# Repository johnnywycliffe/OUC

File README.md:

# Open Underglow Controller (OUC)
This project is designed to provide a better underglow control scheme than the one that comes with the LED strips. It has it's own controls, a small OLED screen, and a connector to the CANBUS for connecting to the car.

## Features
 - ESP 32 controller for fast LED updates
 - 256-bit colors for millions of colors
 - Configuarable patterns for uniqueness
 - Animations!
 - Brakes and turn signal controls for extended light modes
 - 4 12v channels to drive Underglow
 - 2 5v channels to drive extra underglow strips
 - CAN BUS connection to use LEDs as car gauges
 - Wifi/Bluetooth mode for phone control
 - Optional screen and joystick controls to bypass need for phone

## Hardware 
In this project are PCB files needed to order a board, parts files for having a board assembled, and 3d files for a 3d printing a case.

A full hardware list can be found in docs/hardware.md

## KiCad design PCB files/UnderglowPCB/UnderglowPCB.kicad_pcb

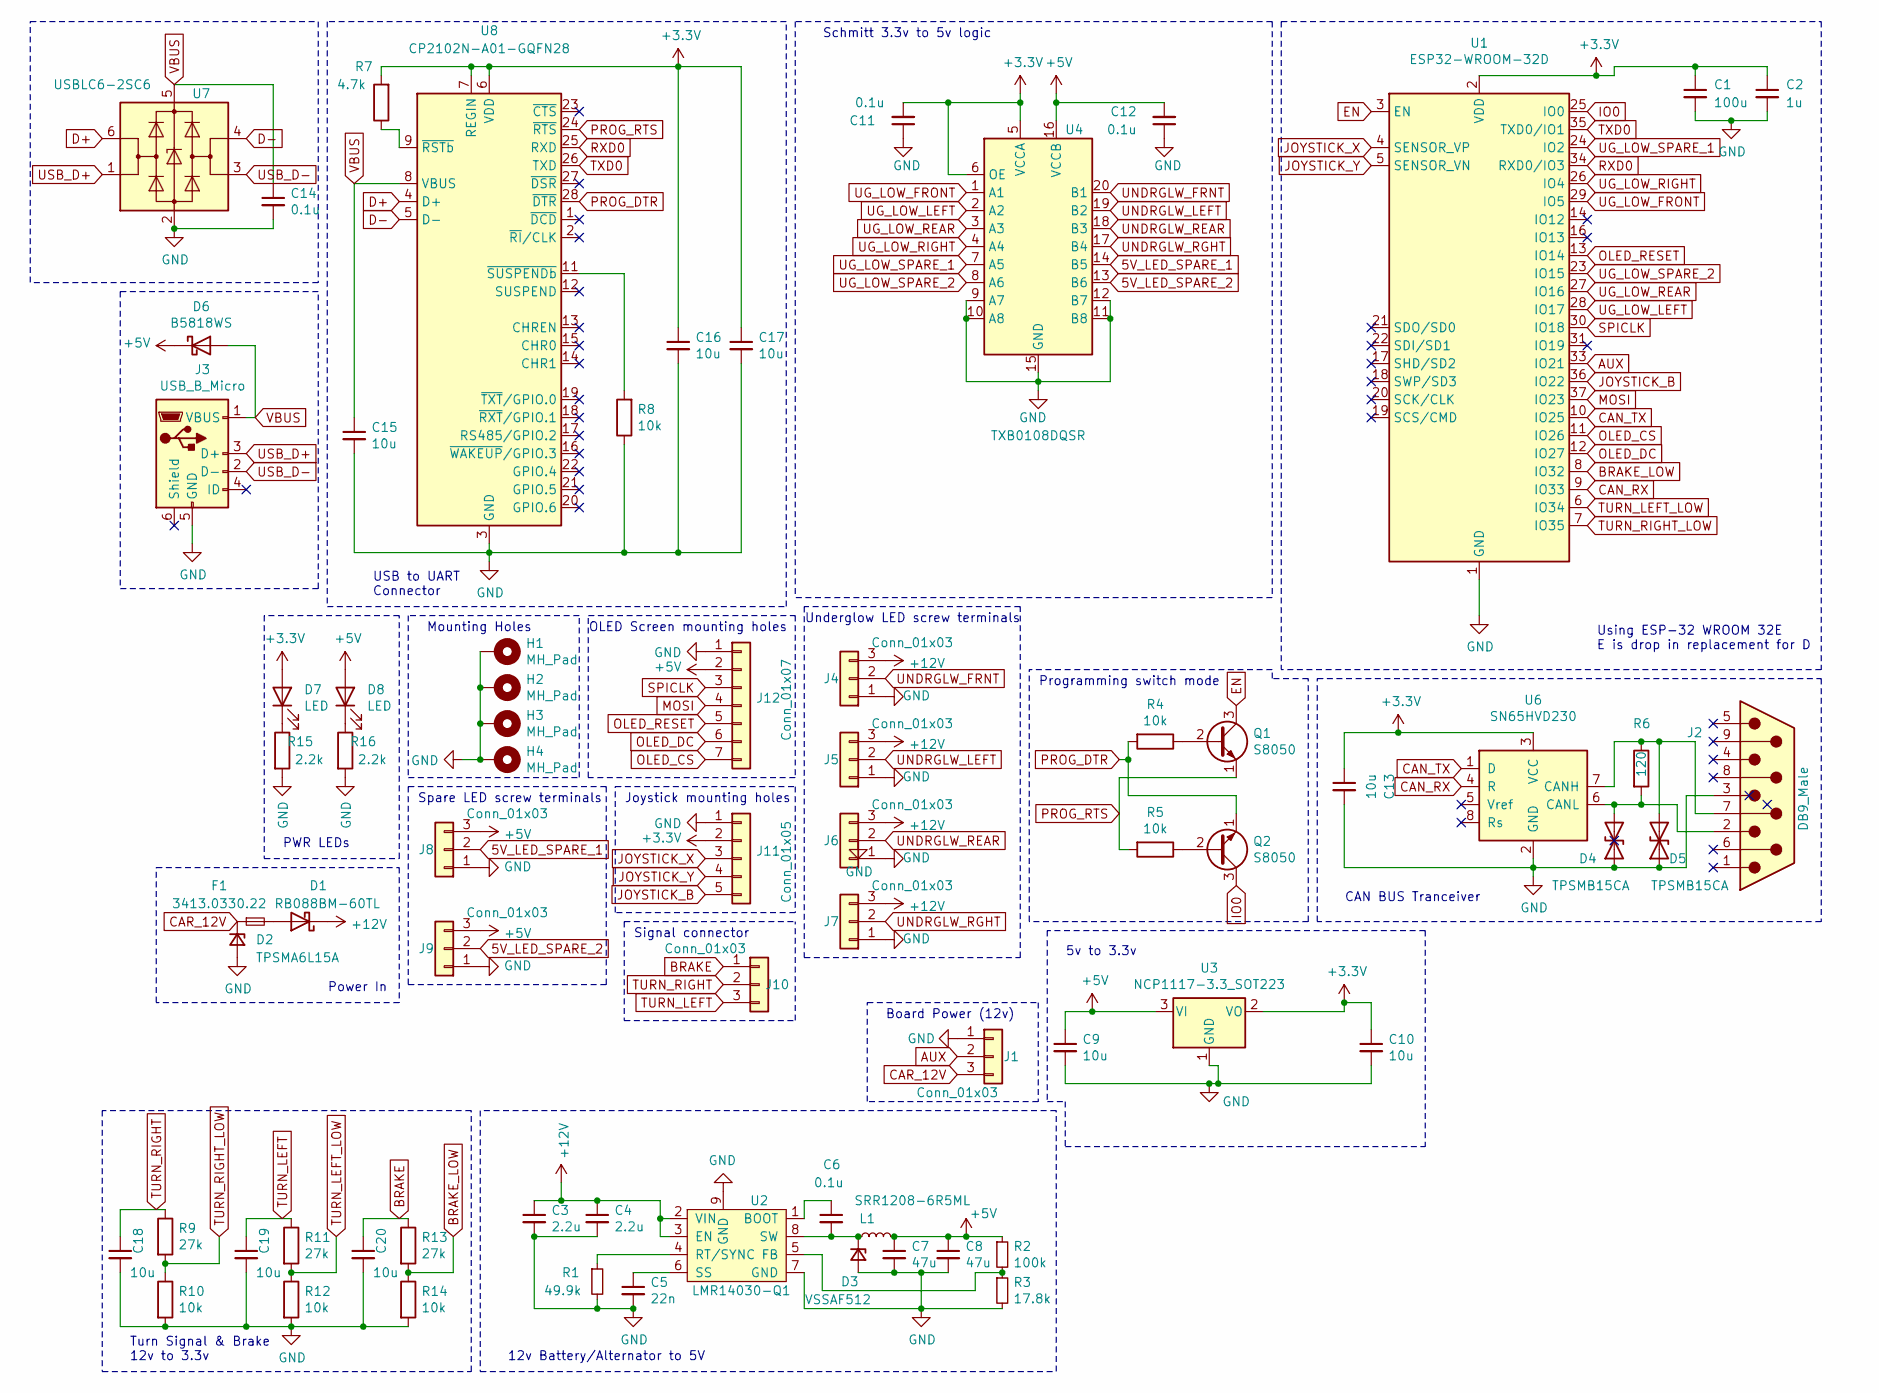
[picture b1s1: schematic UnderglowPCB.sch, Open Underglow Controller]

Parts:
C1: 100u; C_1210_3225Metric
C2: 1u; C_0402_1005Metric
C3, C4: 2.2u; C_0603_1608Metric
C5: 22n; C_0603_1608Metric
C6, C11, C12, C14: 0.1u; C_0603_1608Metric
C7, C8: 47u; C_1210_3225Metric
C9, C10, C13, C15, C16, C17, C18, C19, C20: 10u; C_0603_1608Metric
D1: RB088BM-60TL; TO-252-2_TabPin1
D2: TPSMA6L15A
D3: VSSAF512; DO-221AC
D4, D5: TPSMB15CA
D6: B5818WS; D_SOD-323
D7, D8: LED; LED_0603_1608Metric
F1: 3413.0330.22; Fuse_1206_3216Metric
H1, H2, H3, H4: MH_Pad; MountingHole_4.3mm_M4_Pad_Via
J1, J4, J5, J6, J7, J8, J9, J10: Conn_01x03; PinHeader_1x03_P2.54mm_Vertical
J2: DB9_Male; DB9
J3: USB_B_Micro; USB_Micro-AB_Molex_47590-0001
J11: Conn_01x05; Joystick_Header
J12: Conn_01x07; SSD1306_Footprint
L1: SRR1208-6R5ML; SRR1208
Q1, Q2: S8050; SOT-23
R1: 49.9k; R_0603_1608Metric
R2: 100k; R_0603_1608Metric
R3: 17.8k; R_0603_1608Metric
R4, R5, R8, R10, R12, R14: 10k; R_0603_1608Metric
R6: 120; R_0603_1608Metric
R7: 4.7k; R_0603_1608Metric
R9, R11, R13: 27k; R_0603_1608Metric
R15, R16: 2.2k; R_0603_1608Metric
U1: ESP32-WROOM-32D; ESP32-WROOM-32
U2: LMR14030-Q1; Texas_HSOP-8-1EP_3.9x4.9mm_P1.27mm_ThermalVias
U3: NCP1117-3.3_SOT223; SOT-223-3_TabPin2
U4: TXB0108DQSR; USON-20_2x4mm_P0.4mm
U6: SN65HVD230; Texas_HSOP-8-1EP_3.9x4.9mm_P1.27mm_ThermalVias
U7: USBLC6-2SC6; SOT-23-6
U8: CP2102N-A01-GQFN28; QFN-28-1EP_5x5mm_P0.5mm_EP3.35x3.35mm

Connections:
5V_LED_SPARE_1: J8.2, U4.14 (B5)
5V_LED_SPARE_2: J9.2, U4.13 (B6)
+3V3: C1.1, C2.1, C10.1, C11.2, C13.1, C16.1, C17.1, D7.2 (A), J11.2, R7.2, U1.2 (VDD), U3.2 (VO), U4.5 (VCCA), U4.6 (OE), U6.3 (VCC), U8.6 (VDD), U8.7 (REGIN)
+5V: C7.1, C8.1, C9.1, C12.2, D6.1 (K), D8.2 (A), J8.3, J9.3, J12.2, L1.2, R2.1, U3.3 (VI), U4.16 (VCCB)
+12V: C3.1, C4.1, D1.1 (K), J4.3, J5.3, J6.3, J7.3, U2.2 (VIN), U2.3 (EN)
AUX: J1.2, U1.33 (IO21)
BRAKE: C20.1, J10.1, R13.1
BRAKE_LOW: R13.2, R14.1, U1.8 (IO32)
CAN_RX: U1.9 (IO33), U6.4 (R)
CAN_TX: U1.10 (IO25), U6.1 (D)
CAR_12V: D2.1 (K), F1.1, J1.3
D+: U7.6 (I/O1), U8.4 (D+)
D-: U7.4 (I/O2), U8.5 (D-)
EN: Q1.3 (C), U1.3 (EN)
GND: C1.2, C2.2, C3.2, C4.2, C5.2, C7.2, C8.2, C9.2, C10.2, C11.1, C12.1, C13.2, C14.2, C15.2, C16.2, C17.2, C18.2, C19.2, C20.2, D2.2 (A), D3.2 (A), D4.1 (A1), D5.1 (A1), H1.1, H2.1, H3.1, H4.1, J1.1, J2.3, J3.5 (GND), J4.1, J5.1, J6.1, J7.1, J8.1, J9.1, J11.1, J12.1, R1.2, R3.2, R8.1, R10.2, R12.2, R14.2, R15.2, R16.2, U1.1 (GND), U1.15 (GND), U1.38 (GND), U1.39 (GND), U2.7 (GND), U2.9 (GND), U3.1 (GND), U4.9 (A7), U4.10 (A8), U4.11 (B8), U4.12 (B7), U4.15 (GND), U6.2 (GND), U7.2 (GND), U8.3 (GND), U8.29 (GND)
IO0: Q2.3 (C), U1.25 (IO0)
JOYSTICK_B: J11.5, U1.36 (IO22)
JOYSTICK_X: J11.3, U1.4 (SENSOR_VP)
JOYSTICK_Y: J11.4, U1.5 (SENSOR_VN)
MOSI: J12.4, U1.37 (IO23)
unnamed: C5.1, U2.6 (SS)
unnamed: C6.1, U2.1 (BOOT)
unnamed: C6.2, D3.1 (K), L1.1, U2.8 (SW)
unnamed: D1.2 (A), F1.2
unnamed: D4.2 (A2), J2.2, R6.2, U6.6 (CANL)
unnamed: D5.2 (A2), J2.7, R6.1, U6.7 (CANH)
unnamed: D7.1 (K), R15.1
unnamed: D8.1 (K), R16.1
unnamed: Q1.2 (B), R4.1
unnamed: Q2.2 (B), R5.1
unnamed: R1.1, U2.4 (RT/SYNC)
unnamed: R2.2, R3.1, U2.5 (FB)
unnamed: R7.1, U8.9 (~RSTb)
unnamed: R8.2, U8.11 (~SUSPENDb)
OLED_CS: J12.7, U1.11 (IO26)
OLED_DC: J12.6, U1.12 (IO27)
OLED_RESET: J12.5, U1.13 (IO14)
PROG_DTR: Q2.1 (E), R4.2, U8.28 (~DTR)
PROG_RTS: Q1.1 (E), R5.2, U8.24 (~RTS)
RXD0: U1.34 (RXD0/IO3), U8.25 (RXD)
SPICLK: J12.3, U1.30 (IO18)
TURN_LEFT: C19.1, J10.3, R11.1
TURN_LEFT_LOW: R11.2, R12.1, U1.6 (IO34)
TURN_RIGHT: C18.1, J10.2, R9.1
TURN_RIGHT_LOW: R9.2, R10.1, U1.7 (IO35)
TXD0: U1.35 (TXD0/IO1), U8.26 (TXD)
UG_LOW_FRONT: U1.29 (IO5), U4.1 (A1)
UG_LOW_LEFT: U1.28 (IO17), U4.2 (A2)
UG_LOW_REAR: U1.27 (IO16), U4.3 (A3)
UG_LOW_RIGHT: U1.26 (IO4), U4.4 (A4)
UG_LOW_SPARE_1: U1.24 (IO2), U4.7 (A5)
UG_LOW_SPARE_2: U1.23 (IO15), U4.8 (A6)
UNDRGLW_FRNT: J4.2, U4.20 (B1)
UNDRGLW_LEFT: J5.2, U4.19 (B2)
UNDRGLW_REAR: J6.2, U4.18 (B3)
UNDRGLW_RGHT: J7.2, U4.17 (B4)
USB_D+: J3.3 (D+), U7.1 (I/O1)
USB_D-: J3.2 (D-), U7.3 (I/O2)
VBUS: C14.1, C15.1, D6.2 (A), J3.1 (VBUS), U7.5 (VBUS), U8.8 (VBUS)

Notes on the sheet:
12v Battery/Alternator to 5V
Underglow LED screw terminals
Spare LED screw terminals
Using ESP-32 WROOM 32E E is drop in replacement for D
Joystick mounting holes
CAN BUS Tranceiver
OLED Screen mounting holes
Signal connector
USB to UART Connector
Schmitt 3.3v to 5v logic
Turn Signal & Brake 12v to 3.3v
PWR LEDs
5v to 3.3v
Programming switch mode
Board Power (12v)
Mounting Holes
Power In

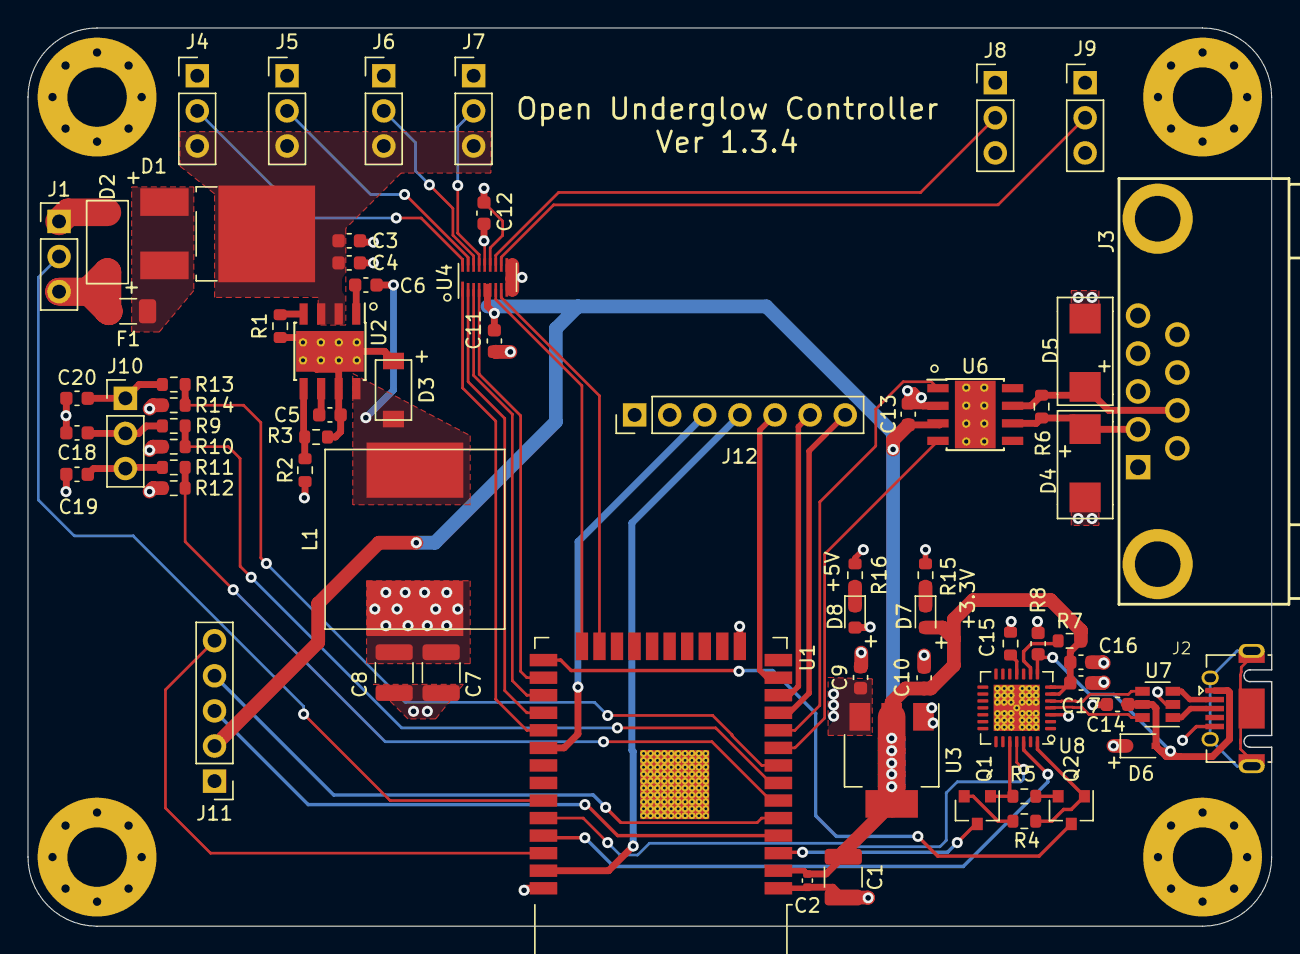
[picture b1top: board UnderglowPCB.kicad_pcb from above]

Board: 4 copper layers, 90.0 x 65.0 mm, 71 parts (0 on the bottom side), 59 nets.

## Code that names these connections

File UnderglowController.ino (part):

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#define DISP_RESET 5
#define DISP_CS 4
#define DISP_DC 2
#define JOYSTICK_X 36
#define JOYSTICK_Y 39
#define JOYSTICK_BUTTON 34
#define BUTTON_0 35
#define LED_FRONT 33
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#define LED_SPARE2 14
#define LTURNSIGNAL 22
#define RTURNSIGNAL 21
#define BRAKE 16
#define RELAY 13
#define CANH 25
#define CANL 17
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
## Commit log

2020-11-12 Documentation updates
2020-11-13 General progress
2020-11-13 Added LED patterns list
2020-11-23 Updated inputs, added new hardware requirements
2020-11-27 Screen working, menu works, need to implement previous menu pointer.
2020-11-30 Menus work, have a hard limit of 100 items. Some documentation updates.
2020-12-05 Began filling menu options
2020-12-05 More menu options filled
2020-12-19 Added in LED initialization. Now only supports WS2811 chipset and clones
2020-12-24 Setting menu expanded, little fixes
2020-12-25 More menus added, but menu untenable. Rework incoming.
2020-12-25 Code refactor in progress; need to figure out how to stuff enum members into void*
2021-01-01 Rewrite stalled, for some reason changing 'selector' inside setMenu causes the program to think there's a passive function, even if there isn't. Need to check bounds.
2021-04-05 PCB design started
2021-04-06 PCB rev 1 schematic complete, custom footprint done.
2021-04-09 Schemtic refined, removed screw terminals, added USB ESD prtection, test points, adjusted paths.
2021-04-09 Version 1.0.0 of PCB is almost done. Need tooling holes and holds for DB9 mount.
2021-04-17 Minor PCB updates
2021-04-18 Posted to reddit, changes include TVS Zener diodes and new power solution. That's a lot bigger.
2021-05-22 Lastest draft of device
2021-05-24 PCB 1.2 finished. Needs some silkscreen work.
2021-05-24 PCB Ver 1.3.2 completed. Documentaion updated to reflect changes. BOM Added to Hardware.md
2021-05-26 PCB data updated, 1.3.2 ordering information is provided.
2021-05-26 Added position files, drill files, gerber files.
2021-05-26 Updated Gerbers to remove x2, updated docs
2021-05-29 Menu issue resolved, continue on.
2021-06-01 Passive items have switch to disangage selector.
2021-06-05 Restructure refactored slightly
2021-06-06 Refactored LED hardware functions in test code.
2021-06-06 New LED pattern test, built off of LED test. Currrently building structure
2021-07-01 Updated PCB to 1.3.4: silkscreen updates for cathode clarification. Test code moving along.
2021-07-01 Continued fleshing out patterntest. Next is init of animations, updating of animations and basic patterns. need to test patterns initialize correctly.
2021-07-05 Patterns can be loaded to device. Animation backup array crashes device.

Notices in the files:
UnderglowController.ino:
Copyright (c) 2020 Jeremy Stintzcum, all rights reserved.
License: MIT
